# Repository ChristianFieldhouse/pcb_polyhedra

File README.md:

## Icosahedron

Kicad files for 3d polyhedrons whose edges are single pcbs.
Mechanical design files (used to create a jig for assembly, dxf pcb edge cuts, power supply, and stand) can be found on onshape: https://cad.onshape.com/documents/2b28f32d3c45028b2ca3b83c/w/f6f68f4f6320d1f011d99ec9/e/1862cafe5ff15b43acebc721?renderMode=0&uiState=65f6e3c7d6b7cf5145787542

first batch of 40 pcbs, produced by PCBWay at a cost of <£10 including shipping. These don't have tounge and groove joints in the corner:

The pcbs were placed in a jig and soldered at the corners (ground is in the very corner, VCC forms a ring around ground)

assempled with LEDs soldered:

Sanded down the LEDs to diffuse the light, cut off the legs of the LEDs, printed a stand:

Tongue and groove versions of icosahedron assembled in the same way

bit more margin for error, so easier to solder the corners

Orange LEDs sanded down (takes some time, diffuse LEDs are available to buy instead!), and soldered on

3d printed power supply case takes USB-C, has a switch, and outputs the right voltage for the LEDs

## Snub Cube

Snub cube pcbs with tongue and groove joints go together in a similar way. There are two different PCBs - the square and triangle edges.

All corners are identical, so you only need one jig, and the jig tells you which of the two edges to use.

All PCBs soldered together

I bought some flat-top LEDs (which are less directional), and tested they run in parallel ok. In the final build I did notice a slight difference in brightness, but it isn't a big effect.

All LEDs soldered (and legs cut off)

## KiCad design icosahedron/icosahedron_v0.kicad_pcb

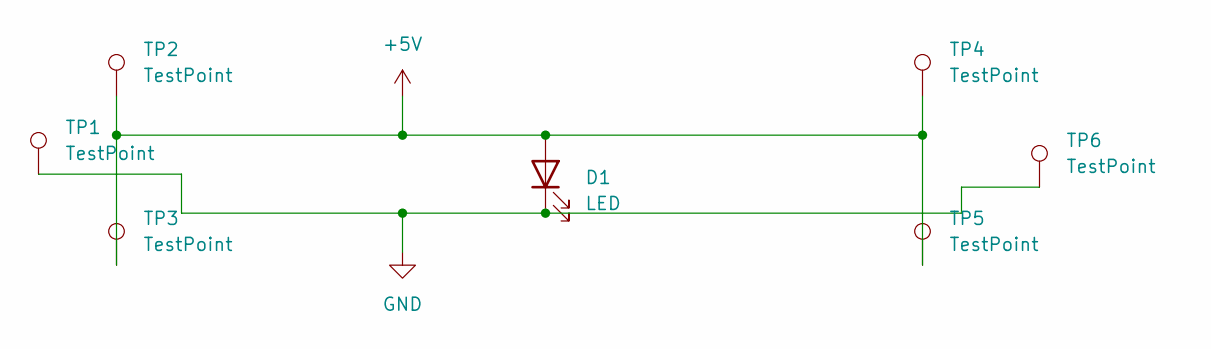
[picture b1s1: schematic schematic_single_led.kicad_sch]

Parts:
D1: LED; LED_D3.0mm
TP1, TP2, TP3, TP4, TP5, TP6: TestPoint; TestPoint_Pad_2.5x2.5mm

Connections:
+5V: D1.2 (A), TP2.1, TP3.1, TP4.1, TP5.1
GND: D1.1 (K), TP1.1, TP6.1

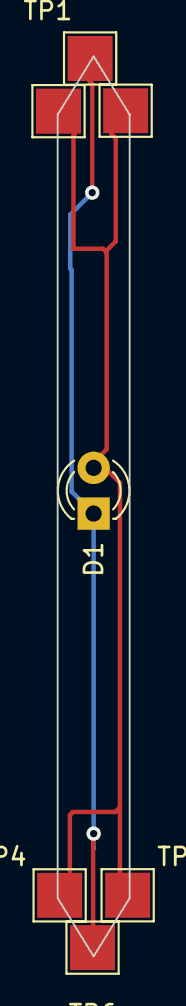
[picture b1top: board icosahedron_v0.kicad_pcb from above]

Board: 2 copper layers, 4.0 x 50.0 mm, 7 parts (0 on the bottom side), 2 nets.

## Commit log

2024-03-17 add gitignore
2024-03-17 add schematic
2024-03-17 snub_cube kicad files
2024-03-17 gitignore more kicad files
2024-04-10 add snub cube to readme
